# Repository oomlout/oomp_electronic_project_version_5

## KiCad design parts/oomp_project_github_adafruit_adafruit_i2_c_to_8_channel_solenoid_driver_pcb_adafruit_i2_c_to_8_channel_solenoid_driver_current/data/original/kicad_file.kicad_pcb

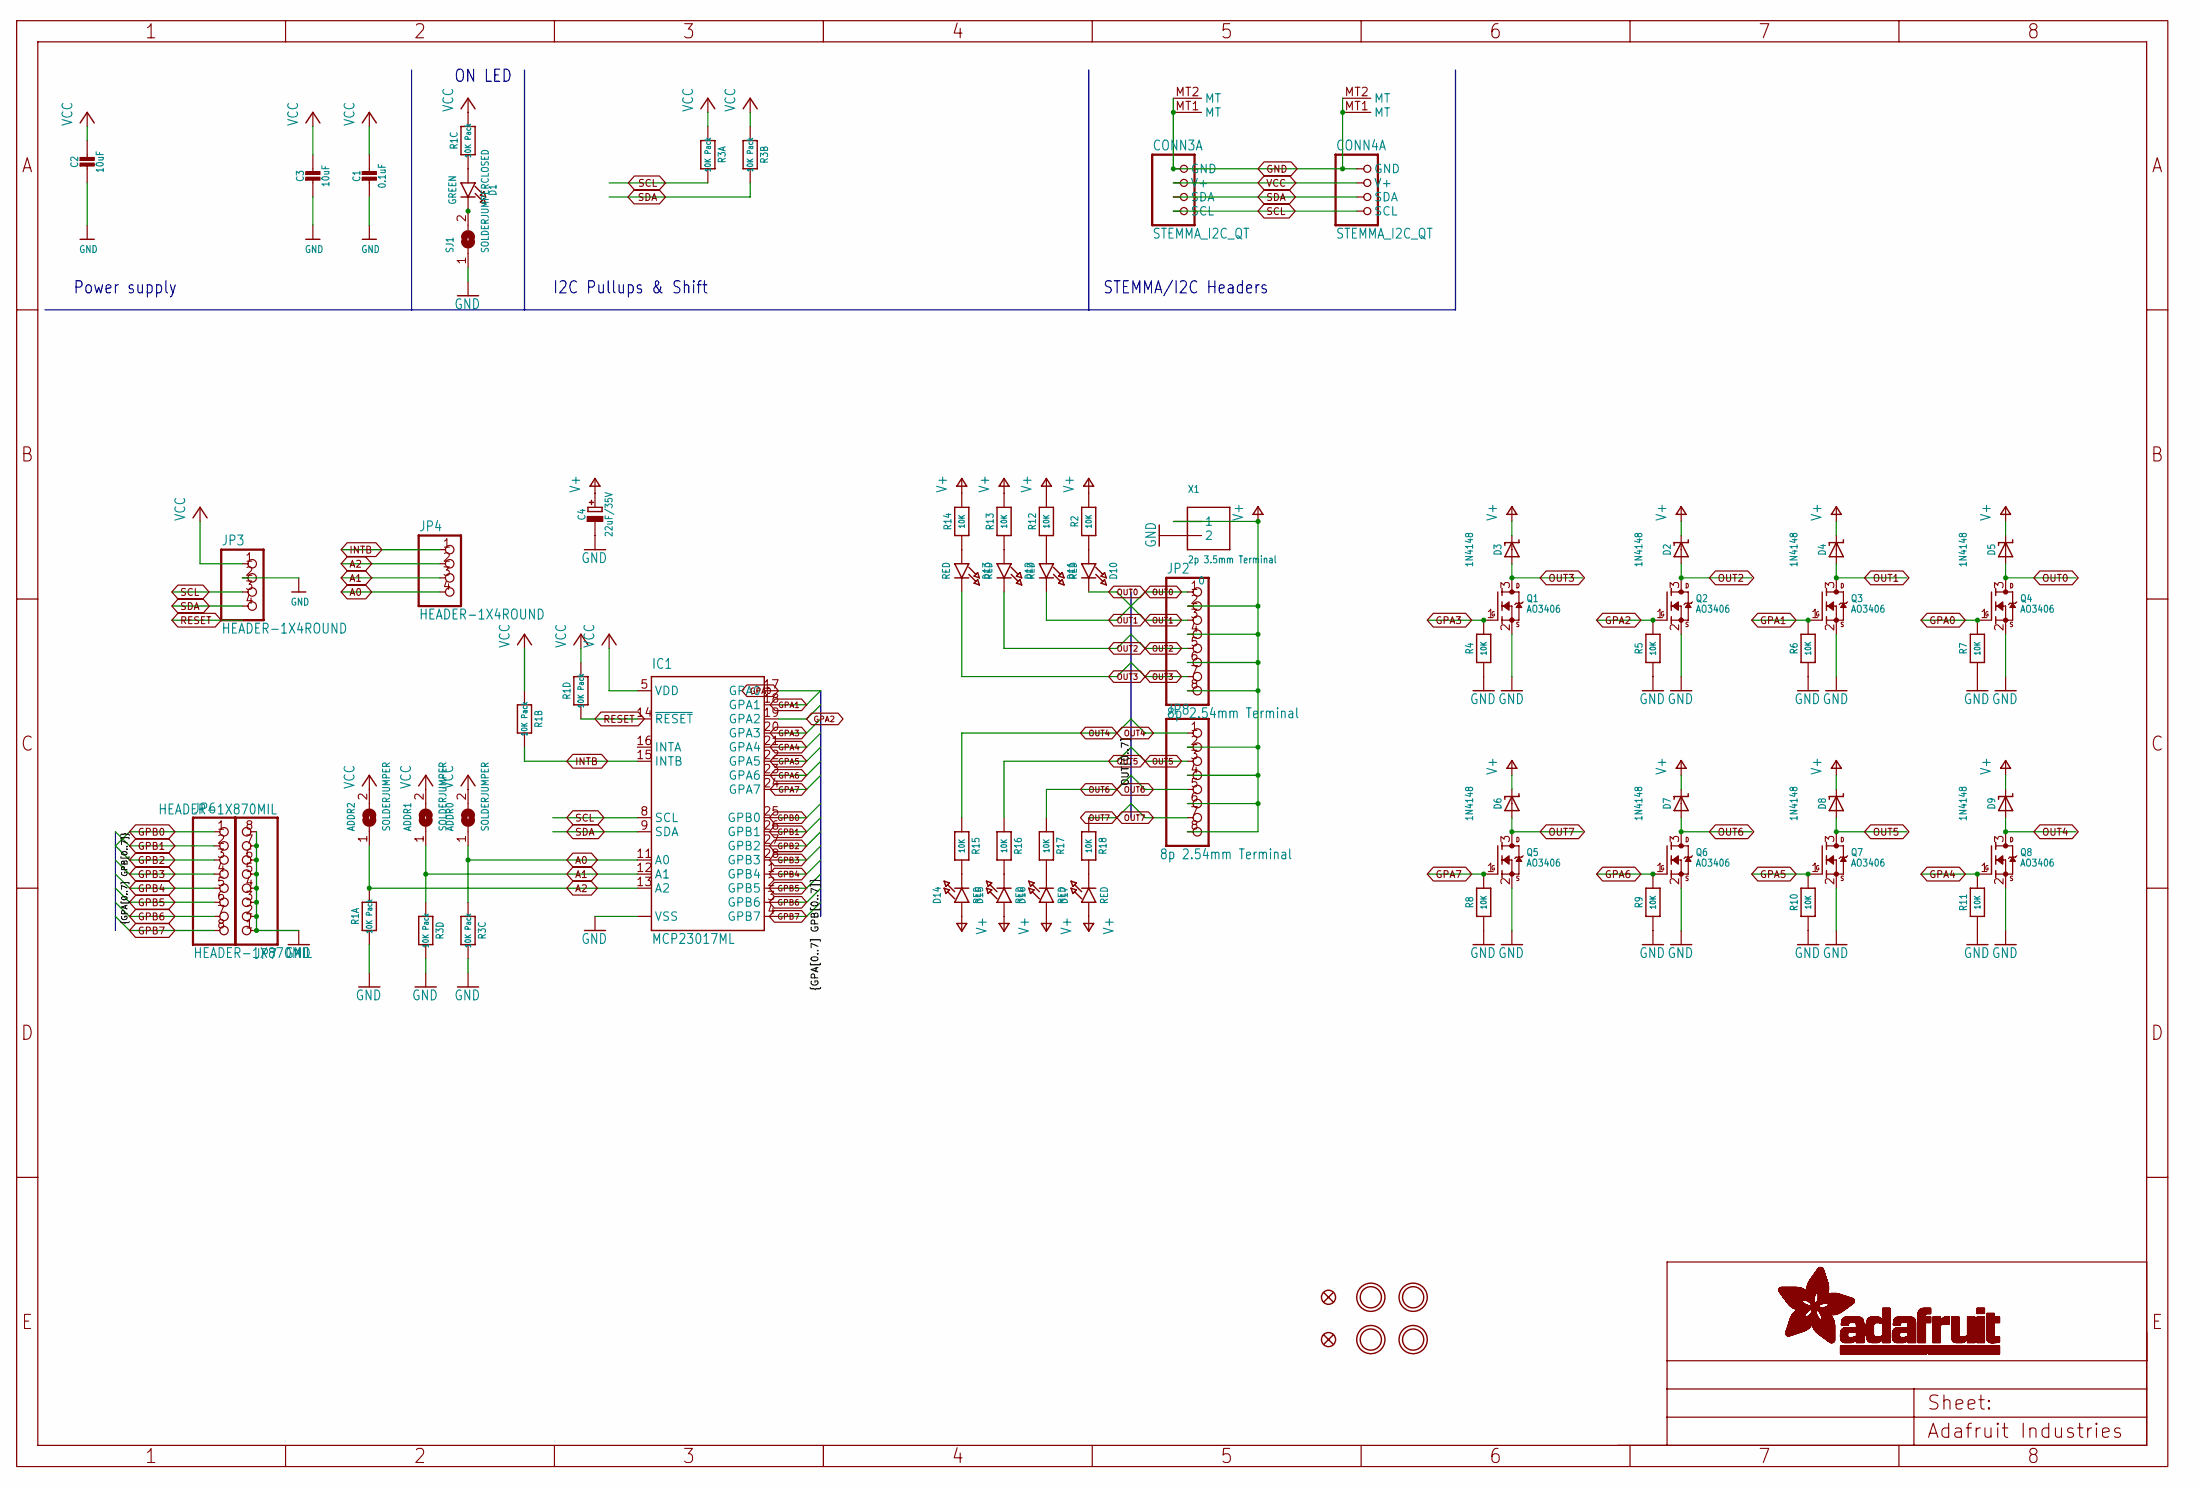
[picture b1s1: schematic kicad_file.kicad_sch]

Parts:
ADDR0, ADDR1, ADDR2: SOLDERJUMPER; SOLDERJUMPER_ARROW_NOPASTE
C1: 0.1uF; 0603-NO
C2, C3: 10uF; 0805-NO
C4: 22uF/35V; PANASONIC_C
CONN3, CONN4: STEMMA_I2C_QT; JST_SH4; LCSC C2845363
D1: GREEN; CHIPLED_0603_NOOUTLINE
D2, D3, D4, D5, D6, D7, D8, D9: 1N4148; SOD-323
D10, D11, D12, D13, D14, D15, D16, D17: RED; CHIPLED_0603_NOOUTLINE
FID3, FID4: FIDUCIAL_1MM
IC1: MCP23017ML; QFN28-ML_6X6MM; MPN MCP23017-E/ML
JP2, JP8: 8p 2.54mm Terminal; 1X08_2.54MMTERMINAL
JP3, JP4: HEADER-1X4ROUND; 1X04_ROUND
JP6, JP7: HEADER-1X870MIL; 1X08_ROUND_70
Q1, Q2, Q3, Q4, Q5, Q6, Q7, Q8: AO3406; SOT23-WIDE
R1, R3: 10K Pack; RESPACK_4X0603
R2, R4, R5, R6, R7, R8, R9, R10, R11, R12, R13, R14, R15, R16, R17, R18: 10K; 0603-NO
SJ1: SOLDERJUMPERCLOSED; SOLDERJUMPER_CLOSEDWIRE
U$1, U$17, U$19, U$21: MOUNTINGHOLE2.5; MOUNTINGHOLE_2.5_PLATED
X1: 2p 3.5mm Terminal; TERMBLOCK_1X2-3.5MM

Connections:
A0: ADDR0.1, IC1.11 (A0), JP4.4, R3.3 (1)
A1: ADDR1.1, IC1.12 (A1), JP4.3, R3.4 (1)
A2: ADDR2.1, IC1.13 (A2), JP4.2, R1.8 (2)
GND: C1.2, C2.2, C3.2, C4.-, CONN3.1 (GND), CONN3.MT1 (MT), CONN3.MT2 (MT), CONN4.1 (GND), CONN4.MT1 (MT), CONN4.MT2 (MT), IC1.6 (VSS), IC1.EXP (VSS), JP3.2, JP7.1, JP7.2, JP7.3, JP7.4, JP7.5, JP7.6, JP7.7, JP7.8, Q1.2 (S), Q2.2 (S), Q3.2 (S), Q4.2 (S), Q5.2 (S), Q6.2 (S), Q7.2 (S), Q8.2 (S), R1.1, R3.5 (2), R3.6 (2), R4.1, R5.1, R6.1, R7.1, R8.1, R9.1, R10.1, R11.1, SJ1.1, X1.2
GPA0: IC1.17 (GPA0), Q4.1 (G), R7.2
GPA1: IC1.18 (GPA1), Q3.1 (G), R6.2
GPA2: IC1.19 (GPA2), Q2.1 (G), R5.2
GPA3: IC1.20 (GPA3), Q1.1 (G), R4.2
GPA4: IC1.21 (GPA4), Q8.1 (G), R11.2
GPA5: IC1.22 (GPA5), Q7.1 (G), R10.2
GPA6: IC1.23 (GPA6), Q6.1 (G), R9.2
GPA7: IC1.24 (GPA7), Q5.1 (G), R8.2
GPB0: IC1.25 (GPB0), JP6.1
GPB1: IC1.26 (GPB1), JP6.2
GPB2: IC1.27 (GPB2), JP6.3
GPB3: IC1.28 (GPB3), JP6.4
GPB4: IC1.1 (GPB4), JP6.5
GPB5: IC1.2 (GPB5), JP6.6
GPB6: IC1.3 (GPB6), JP6.7
GPB7: IC1.4 (GPB7), JP6.8
INTB: IC1.15 (INTB), JP4.1, R1.7 (2)
unnamed: D1.A, R1.3 (1)
unnamed: D1.C, SJ1.2
unnamed: D10.A, R2.1
unnamed: D11.A, R12.1
unnamed: D12.A, R13.1
unnamed: D13.A, R14.1
unnamed: D14.C, R15.2
unnamed: D15.C, R16.2
unnamed: D16.C, R17.2
unnamed: D17.C, R18.2
OUT0: D5.A, D10.C, JP2.1, Q4.3 (D)
OUT1: D4.A, D11.C, JP2.3, Q3.3 (D)
OUT2: D2.A, D12.C, JP2.5, Q2.3 (D)
OUT3: D3.A, D13.C, JP2.7, Q1.3 (D)
OUT4: D9.A, JP8.1, Q8.3 (D), R15.1
OUT5: D8.A, JP8.3, Q7.3 (D), R16.1
OUT6: D7.A, JP8.5, Q6.3 (D), R17.1
OUT7: D6.A, JP8.7, Q5.3 (D), R18.1
RESET: IC1.14 (~RESET), R1.4 (1)
SCL: CONN3.4 (SCL), CONN4.4 (SCL), IC1.8 (SCL), JP3.3, R3.8 (2)
SDA: CONN3.3 (SDA), CONN4.3 (SDA), IC1.9 (SDA), JP3.4, R3.7 (2)
V+: C4.+, D2.C, D3.C, D4.C, D5.C, D6.C, D7.C, D8.C, D9.C, D14.A, D15.A, D16.A, D17.A, JP2.2, JP2.4, JP2.6, JP2.8, JP8.2, JP8.4, JP8.6, JP8.8, R2.2, R12.2, R13.2, R14.2, X1.1
VCC: ADDR0.2, ADDR1.2, ADDR2.2, C1.1, C2.1, C3.1, CONN3.2 (V+), CONN4.2 (V+), IC1.5 (VDD), JP3.1, R1.2 (1), R1.5 (2), R1.6 (2), R3.1, R3.2 (1)

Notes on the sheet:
STEMMA/I2C Headers
ON LED
I2C Pullups & Shift
Power supply

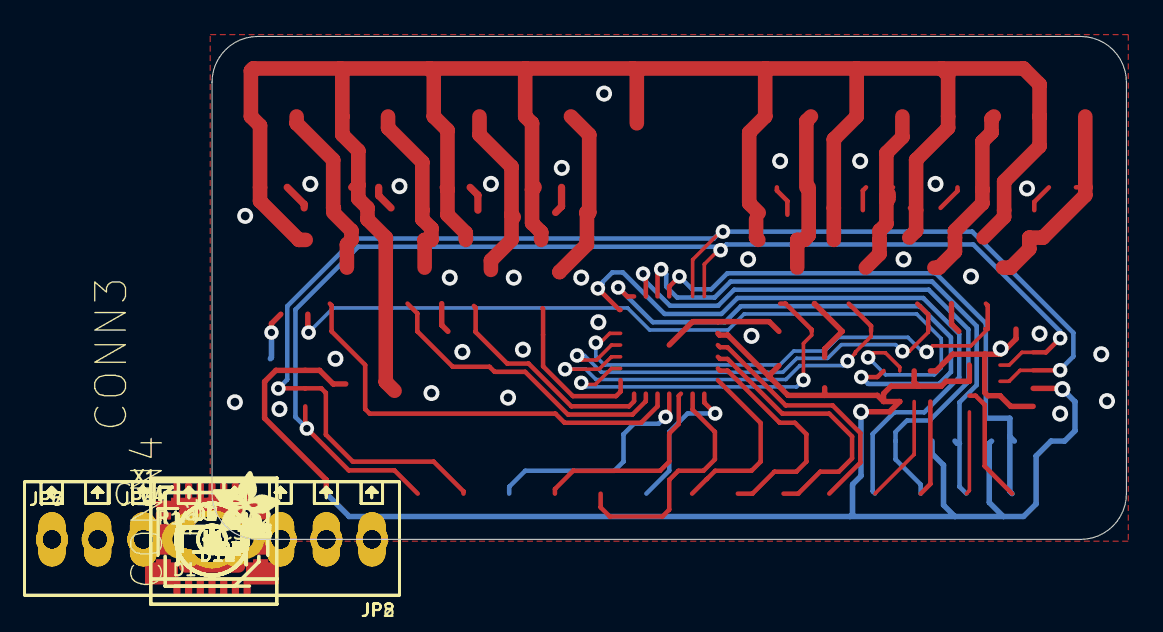
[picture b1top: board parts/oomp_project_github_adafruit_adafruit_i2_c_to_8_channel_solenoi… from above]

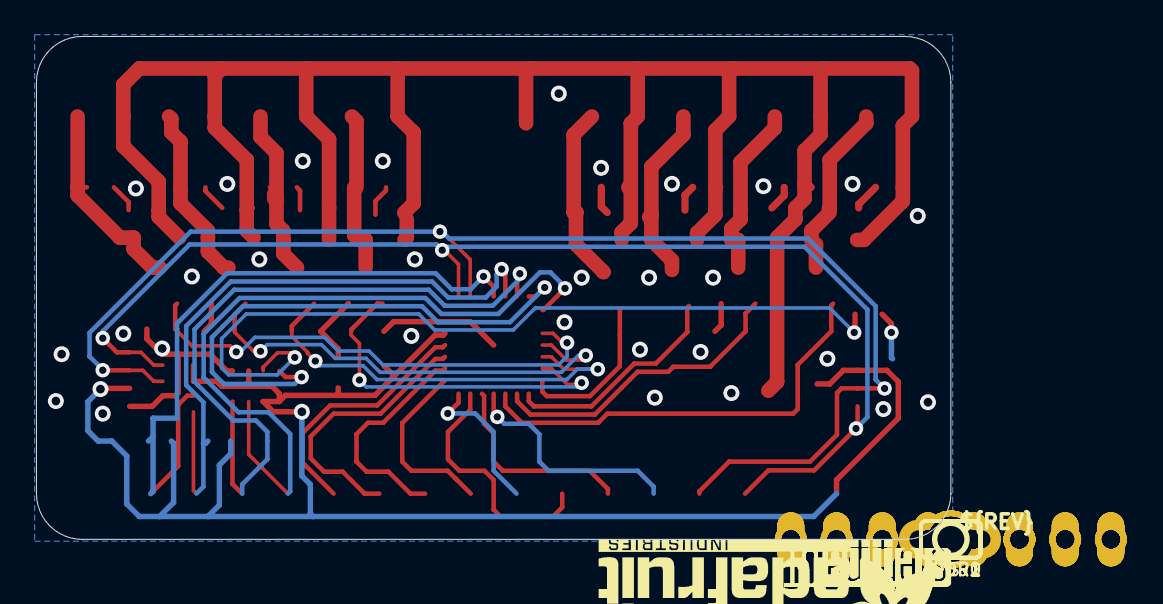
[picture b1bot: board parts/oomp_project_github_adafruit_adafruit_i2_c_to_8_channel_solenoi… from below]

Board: 2 copper layers, 50.8 x 27.9 mm, 135 parts (32 on the bottom side), 44 nets.

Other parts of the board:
PLABEL0: PLABEL0
PLABEL1: PLABEL1
PLABEL2: PLABEL2
PLABEL3: PLABEL3
PLABEL4: PLABEL4
PLABEL5: PLABEL5
PLABEL6: PLABEL6
PLABEL7: PLABEL7
PLABEL8: PLABEL8
PLABEL9: PLABEL9
PLABEL10: PLABEL10
PLABEL11: PLABEL11
PLABEL12: PLABEL12
PLABEL13: PLABEL13
PLABEL14: PLABEL14
PLABEL15: PLABEL15
PLABEL16: PLABEL16
PLABEL17: PLABEL17
PLABEL18: PLABEL18
PLABEL19: PLABEL19
PLABEL20: PLABEL20
PLABEL21: PLABEL21
PLABEL22: PLABEL22
PLABEL23: PLABEL23
PLABEL24: PLABEL24
PLABEL25: PLABEL25
PLABEL26: PLABEL26
PLABEL27: PLABEL27
PLABEL28: PLABEL28
PLABEL29: PLABEL29
PLABEL30: PLABEL30
PLABEL31: PLABEL31
PLABEL32: PLABEL32
PLABEL33: PLABEL33
PLABEL34: PLABEL34
PLABEL35: PLABEL35
PLABEL36: PLABEL36
PLABEL37: PLABEL37
PLABEL38: PLABEL38
PLABEL39: PLABEL39
PLABEL40: PLABEL40
PLABEL41: PLABEL41
PLABEL42: PLABEL42
PLABEL43: PLABEL43
PLABEL44: PLABEL44
PLABEL45: PLABEL45
PLABEL46: PLABEL46
PLABEL47: PLABEL47
PLABEL48: PLABEL48
PLABEL49: PLABEL49
PLABEL50: PLABEL50
PLABEL51: PLABEL51
PLABEL52: PLABEL52
PLABEL53: PLABEL53
PLABEL54: PLABEL54
PLABEL55: PLABEL55
PLABEL56: PLABEL56
PLABEL57: PLABEL57
PLABEL58: PLABEL58
PLABEL59: PLABEL59
PLABEL60: PLABEL60
U$2: PLUS; SYMBOL_PLUS
U$3: SYMBOL_MINUS
U$4: ADAFRUIT_3.5MM
U$7: ADAFRUIT_TEXT_20MM
U$25: PCBFEAT-REV-040
U$30, U$31: STEMMAQT

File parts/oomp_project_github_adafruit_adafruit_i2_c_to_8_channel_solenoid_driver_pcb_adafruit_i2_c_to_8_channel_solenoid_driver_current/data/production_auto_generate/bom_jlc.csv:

Comment,Designator,Footprint,LCSC Part #
,"JP3,JP4",Adafruit I2C to 8 Channel Solenoid Driver-import-fps:1X04_ROUND,C42431795
,"JP6,JP7",Adafruit I2C to 8 Channel Solenoid Driver-import-fps:1X08_ROUND_70,C492421
,U$4,Adafruit I2C to 8 Channel Solenoid Driver-import-fps:ADAFRUIT_3.5MM,
,U$7,Adafruit I2C to 8 Channel Solenoid Driver-import-fps:ADAFRUIT_TEXT_20MM,
,U$25,Adafruit I2C to 8 Channel Solenoid Driver-import-fps:PCBFEAT-REV-040,
,PLABEL0,Adafruit I2C to 8 Channel Solenoid Driver-import-fps:PLABEL0,
,PLABEL1,Adafruit I2C to 8 Channel Solenoid Driver-import-fps:PLABEL1,
,PLABEL10,Adafruit I2C to 8 Channel Solenoid Driver-import-fps:PLABEL10,
,PLABEL11,Adafruit I2C to 8 Channel Solenoid Driver-import-fps:PLABEL11,
,PLABEL12,Adafruit I2C to 8 Channel Solenoid Driver-import-fps:PLABEL12,
,PLABEL13,Adafruit I2C to 8 Channel Solenoid Driver-import-fps:PLABEL13,
,PLABEL14,Adafruit I2C to 8 Channel Solenoid Driver-import-fps:PLABEL14,
,PLABEL15,Adafruit I2C to 8 Channel Solenoid Driver-import-fps:PLABEL15,
,PLABEL16,Adafruit I2C to 8 Channel Solenoid Driver-import-fps:PLABEL16,
,PLABEL17,Adafruit I2C to 8 Channel Solenoid Driver-import-fps:PLABEL17,
,PLABEL18,Adafruit I2C to 8 Channel Solenoid Driver-import-fps:PLABEL18,
,PLABEL19,Adafruit I2C to 8 Channel Solenoid Driver-import-fps:PLABEL19,
,PLABEL2,Adafruit I2C to 8 Channel Solenoid Driver-import-fps:PLABEL2,
,PLABEL20,Adafruit I2C to 8 Channel Solenoid Driver-import-fps:PLABEL20,
,PLABEL21,Adafruit I2C to 8 Channel Solenoid Driver-import-fps:PLABEL21,
,PLABEL22,Adafruit I2C to 8 Channel Solenoid Driver-import-fps:PLABEL22,
,PLABEL23,Adafruit I2C to 8 Channel Solenoid Driver-import-fps:PLABEL23,
,PLABEL24,Adafruit I2C to 8 Channel Solenoid Driver-import-fps:PLABEL24,
,PLABEL25,Adafruit I2C to 8 Channel Solenoid Driver-import-fps:PLABEL25,
,PLABEL26,Adafruit I2C to 8 Channel Solenoid Driver-import-fps:PLABEL26,
,PLABEL27,Adafruit I2C to 8 Channel Solenoid Driver-import-fps:PLABEL27,
,PLABEL28,Adafruit I2C to 8 Channel Solenoid Driver-import-fps:PLABEL28,
,PLABEL29,Adafruit I2C to 8 Channel Solenoid Driver-import-fps:PLABEL29,
,PLABEL3,Adafruit I2C to 8 Channel Solenoid Driver-import-fps:PLABEL3,
,PLABEL30,Adafruit I2C to 8 Channel Solenoid Driver-import-fps:PLABEL30,
,PLABEL31,Adafruit I2C to 8 Channel Solenoid Driver-import-fps:PLABEL31,
,PLABEL32,Adafruit I2C to 8 Channel Solenoid Driver-import-fps:PLABEL32,
,PLABEL33,Adafruit I2C to 8 Channel Solenoid Driver-import-fps:PLABEL33,
,PLABEL34,Adafruit I2C to 8 Channel Solenoid Driver-import-fps:PLABEL34,
,PLABEL35,Adafruit I2C to 8 Channel Solenoid Driver-import-fps:PLABEL35,
,PLABEL36,Adafruit I2C to 8 Channel Solenoid Driver-import-fps:PLABEL36,
,PLABEL37,Adafruit I2C to 8 Channel Solenoid Driver-import-fps:PLABEL37,
,PLABEL38,Adafruit I2C to 8 Channel Solenoid Driver-import-fps:PLABEL38,
,PLABEL39,Adafruit I2C to 8 Channel Solenoid Driver-import-fps:PLABEL39,
,PLABEL4,Adafruit I2C to 8 Channel Solenoid Driver-import-fps:PLABEL4,
,PLABEL40,Adafruit I2C to 8 Channel Solenoid Driver-import-fps:PLABEL40,
,PLABEL41,Adafruit I2C to 8 Channel Solenoid Driver-import-fps:PLABEL41,
,PLABEL42,Adafruit I2C to 8 Channel Solenoid Driver-import-fps:PLABEL42,
,PLABEL43,Adafruit I2C to 8 Channel Solenoid Driver-import-fps:PLABEL43,
,PLABEL44,Adafruit I2C to 8 Channel Solenoid Driver-import-fps:PLABEL44,
,PLABEL45,Adafruit I2C to 8 Channel Solenoid Driver-import-fps:PLABEL45,
,PLABEL46,Adafruit I2C to 8 Channel Solenoid Driver-import-fps:PLABEL46,
,PLABEL47,Adafruit I2C to 8 Channel Solenoid Driver-import-fps:PLABEL47,
,PLABEL48,Adafruit I2C to 8 Channel Solenoid Driver-import-fps:PLABEL48,
,PLABEL49,Adafruit I2C to 8 Channel Solenoid Driver-import-fps:PLABEL49,
,PLABEL5,Adafruit I2C to 8 Channel Solenoid Driver-import-fps:PLABEL5,
,PLABEL50,Adafruit I2C to 8 Channel Solenoid Driver-import-fps:PLABEL50,
,PLABEL51,Adafruit I2C to 8 Channel Solenoid Driver-import-fps:PLABEL51,
,PLABEL52,Adafruit I2C to 8 Channel Solenoid Driver-import-fps:PLABEL52,
,PLABEL53,Adafruit I2C to 8 Channel Solenoid Driver-import-fps:PLABEL53,
,PLABEL54,Adafruit I2C to 8 Channel Solenoid Driver-import-fps:PLABEL54,
,PLABEL55,Adafruit I2C to 8 Channel Solenoid Driver-import-fps:PLABEL55,
,PLABEL56,Adafruit I2C to 8 Channel Solenoid Driver-import-fps:PLABEL56,
,PLABEL57,Adafruit I2C to 8 Channel Solenoid Driver-import-fps:PLABEL57,
,PLABEL58,Adafruit I2C to 8 Channel Solenoid Driver-import-fps:PLABEL58,
,PLABEL59,Adafruit I2C to 8 Channel Solenoid Driver-import-fps:PLABEL59,
,PLABEL6,Adafruit I2C to 8 Channel Solenoid Driver-import-fps:PLABEL6,
,PLABEL60,Adafruit I2C to 8 Channel Solenoid Driver-import-fps:PLABEL60,
,PLABEL7,Adafruit I2C to 8 Channel Solenoid Driver-import-fps:PLABEL7,
,PLABEL8,Adafruit I2C to 8 Channel Solenoid Driver-import-fps:PLABEL8,
,PLABEL9,Adafruit I2C to 8 Channel Solenoid Driver-import-fps:PLABEL9,
,"ADDR0,ADDR1,ADDR2",Adafruit I2C to 8 Channel Solenoid Driver-import-fps:SOLDERJUMPER_ARROW_NOPASTE,
,"U$30,U$31",Adafruit I2C to 8 Channel Solenoid Driver-import-fps:STEMMAQT,
,U$3,Adafruit I2C to 8 Channel Solenoid Driver-import-fps:SYMBOL_MINUS,
0.1uF,C1,Adafruit I2C to 8 Channel Solenoid Driver-import-fps:0603-NO,C14663
10K,"R2,R4,R5,R6,R7,R8,R9,R10,R11,R12,R13,R14,R15,R16,R17,R18",Adafruit I2C to 8 Channel Solenoid Driver-import-fps:0603-NO,C98220
10K Pack,"R1,R3",Adafruit I2C to 8 Channel Solenoid Driver-import-fps:RESPACK_4X0603,C98220
10uF,"C2,C3",Adafruit I2C to 8 Channel Solenoid Driver-import-fps:0805-NO,
1N4148,"D2,D3,D4,D5,D6,D7,D8,D9",Adafruit I2C to 8 Channel Solenoid Driver-import-fps:SOD-323,
22uF/35V,C4,Adafruit I2C to 8 Channel Solenoid Driver-import-fps:PANASONIC_C,
2p 3.5mm Terminal,X1,Adafruit I2C to 8 Channel Solenoid Driver-import-fps:TERMBLOCK_1X2-3.5MM,
8p 2.54mm Terminal,"JP2,JP8",Adafruit I2C to 8 Channel Solenoid Driver-import-fps:1X08_2.54MMTERMINAL,C492421
AO3406,"Q1,Q2,Q3,Q4,Q5,Q6,Q7,Q8",Adafruit I2C to 8 Channel Solenoid Driver-import-fps:SOT23-WIDE,
GREEN,D1,Adafruit I2C to 8 Channel Solenoid Driver-import-fps:CHIPLED_0603_NOOUTLINE,
MCP23017ML,IC1,Adafruit I2C to 8 Channel Solenoid Driver-import-fps:QFN28-ML_6X6MM,
PLUS,U$2,Adafruit I2C to 8 Channel Solenoid Driver-import-fps:SYMBOL_PLUS,
RED,"D10,D11,D12,D13,D14,D15,D16,D17",Adafruit I2C to 8 Channel Solenoid Driver-import-fps:CHIPLED_0603_NOOUTLINE,
STEMMA_I2C_QT,"CONN3,CONN4",Adafruit I2C to 8 Channel Solenoid Driver-import-fps:JST_SH4,C160404

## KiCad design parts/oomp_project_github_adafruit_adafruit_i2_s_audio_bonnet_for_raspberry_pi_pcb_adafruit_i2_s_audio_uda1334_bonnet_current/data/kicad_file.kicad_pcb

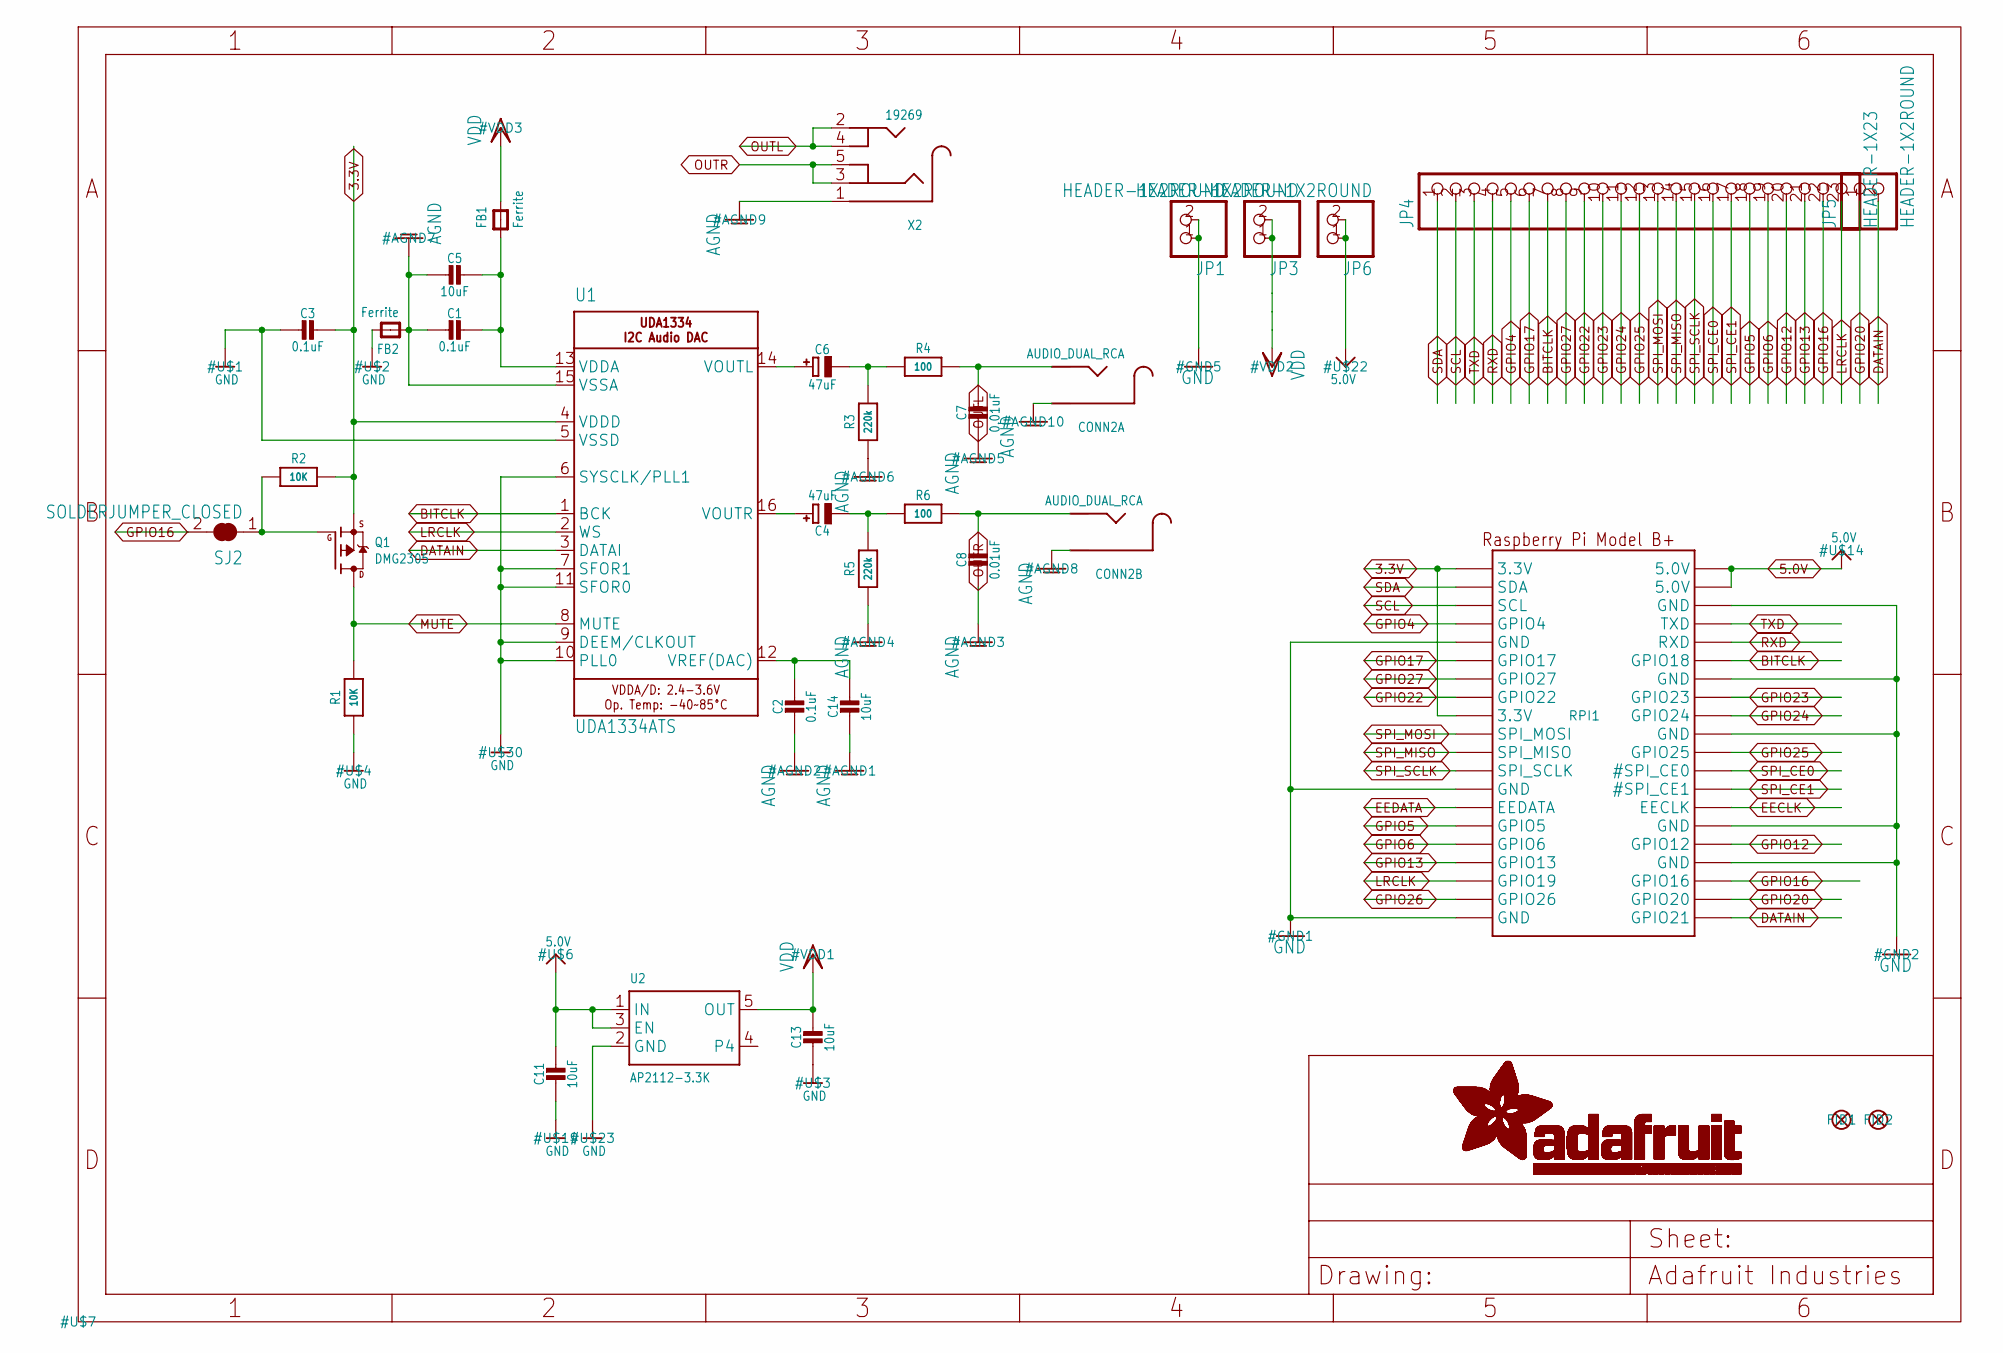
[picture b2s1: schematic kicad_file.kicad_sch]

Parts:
C1, C2, C3: 0.1uF; 0603-NO
C4, C6: 47uF; PANASONIC_C
C5, C11, C13, C14: 10uF; 0805-NO
C7, C8: 0.01uF; 0603-NO
CONN2: AUDIO_DUAL_RCA; RCA_DUAL_JACK
FB1, FB2: Ferrite; 0805
FID1, FID2: FIDUCIAL_1MM
JP1, JP3, JP5, JP6: HEADER-1X2ROUND; 1X02_ROUND
JP4: HEADER-1X23; 1X23_ROUND_70MIL
Q1: DMG2305; SOT23-WIDE
R1, R2: 10K; 0603-NO
R3, R5: 220k; 0603-NO
R4, R6: 100; 0603-NO
RPI1: RASPBERRYPI_BPLUS_BONNET_THMSMT; PI_BONNET_THMSMT
SJ2: SOLDERJUMPER_CLOSED; SOLDERJUMPER_CLOSEDWIRE
U1: UDA1334ATS; SSOP16_4.4MM
U2: AP2112-3.3K; SOT23-5
X2: 19269; 4UCONN_19269

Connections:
3.3V: C3.1, Q1.2 (S), R2.2, RPI1.1 (3.3V), RPI1.17 (3.3V), RPI1.S1 (3.3V), RPI1.S17 (3.3V), U1.4 (VDDD)
5.0V: C11.1, JP6.1, JP6.2, RPI1.2 (5.0V), RPI1.4 (5.0V), RPI1.S2 (5.0V), RPI1.S4 (5.0V), U2.1 (IN), U2.3 (EN)
AGND: C1.2, C2.2, C5.2, C7.2, C8.2, C14.2, CONN2.L_G (SLEEVE), CONN2.L_G' (SLEEVE), CONN2.R_G (SLEEVE), CONN2.R_G' (SLEEVE), FB2.1, R3.1, R5.1, U1.15 (VSSA), X2.1
BITCLK: JP4.7, RPI1.12 (GPIO18), RPI1.S12 (GPIO18), U1.1 (BCK)
DATAIN: JP5.2, RPI1.40 (GPIO21), RPI1.S40 (GPIO21), U1.3 (DATAI)
EECLK: RPI1.28 (EECLK), RPI1.S28 (EECLK)
EEDATA: RPI1.27 (EEDATA), RPI1.S27 (EEDATA)
GND: C3.2, C11.2, C13.2, FB2.2, JP1.1, JP1.2, R1.1, RPI1.6 (GND), RPI1.9 (GND), RPI1.14 (GND), RPI1.20 (GND), RPI1.25 (GND), RPI1.30 (GND), RPI1.34 (GND), RPI1.39 (GND), RPI1.S6 (GND), RPI1.S9 (GND), RPI1.S14 (GND), RPI1.S20 (GND), RPI1.S25 (GND), RPI1.S30 (GND), RPI1.S34 (GND), RPI1.S39 (GND), U1.5 (VSSD), U1.6 (SYSCLK/PLL1), U1.7 (SFOR1), U1.9 (DEEM/CLKOUT), U1.10 (PLL0), U1.11 (SFOR0), U2.2 (GND)
GPIO4: JP4.5, RPI1.7 (GPIO4), RPI1.S7 (GPIO4)
GPIO5: JP4.18, RPI1.29 (GPIO5), RPI1.S29 (GPIO5)
GPIO6: JP4.19, RPI1.31 (GPIO6), RPI1.S31 (GPIO6)
GPIO12: JP4.20, RPI1.32 (GPIO12), RPI1.S32 (GPIO12)
GPIO13: JP4.21, RPI1.33 (GPIO13), RPI1.S33 (GPIO13)
GPIO16: JP4.22, RPI1.36 (GPIO16), RPI1.S36 (GPIO16), SJ2.2
GPIO17: JP4.6, RPI1.11 (GPIO17), RPI1.S11 (GPIO17)
GPIO20: JP5.1, RPI1.38 (GPIO20), RPI1.S38 (GPIO20)
GPIO22: JP4.9, RPI1.15 (GPIO22), RPI1.S15 (GPIO22)
GPIO23: JP4.10, RPI1.16 (GPIO23), RPI1.S16 (GPIO23)
GPIO24: JP4.11, RPI1.18 (GPIO24), RPI1.S18 (GPIO24)
GPIO25: JP4.12, RPI1.22 (GPIO25), RPI1.S22 (GPIO25)
GPIO26: RPI1.37 (GPIO26), RPI1.S37 (GPIO26)
GPIO27: JP4.8, RPI1.13 (GPIO27), RPI1.S13 (GPIO27)
LRCLK: JP4.23, RPI1.35 (GPIO19), RPI1.S35 (GPIO19), U1.2 (WS)
MUTE: Q1.3 (D), R1.2, U1.8 (MUTE)
unnamed: C2.1, C14.1, U1.12 (VREF(DAC))
unnamed: C1.1, C5.1, FB1.1, U1.13 (VDDA)
unnamed: C4.+, U1.16 (VOUTR)
unnamed: Q1.1 (G), R2.1, SJ2.1
unnamed: C6.+, U1.14 (VOUTL)
unnamed: C6.-, R3.2, R4.1
unnamed: C4.-, R5.2, R6.1
OUTL: C7.1, CONN2.L_SIG (TIP), CONN2.L_SIG' (TIP), R4.2, X2.2, X2.4
OUTR: C8.1, CONN2.R_SIG (TIP), CONN2.R_SIG' (TIP), R6.2, X2.3, X2.5
RXD: JP4.4, RPI1.10 (RXD), RPI1.S10 (RXD)
SCL: JP4.2, RPI1.5 (SCL), RPI1.S5 (SCL)
SDA: JP4.1, RPI1.3 (SDA), RPI1.S3 (SDA)
SPI_CE0: JP4.16, RPI1.24 (#SPI_CE0), RPI1.S24 (#SPI_CE0)
SPI_CE1: JP4.17, RPI1.26 (#SPI_CE1), RPI1.S26 (#SPI_CE1)
SPI_MISO: JP4.14, RPI1.21 (SPI_MISO), RPI1.S21 (SPI_MISO)
SPI_MOSI: JP4.13, RPI1.19 (SPI_MOSI), RPI1.S19 (SPI_MOSI)
SPI_SCLK: JP4.15, RPI1.23 (SPI_SCLK), RPI1.S23 (SPI_SCLK)
TXD: JP4.3, RPI1.8 (TXD), RPI1.S8 (TXD)
VDD: C13.1, FB1.2, JP3.1, JP3.2, U2.5 (OUT)

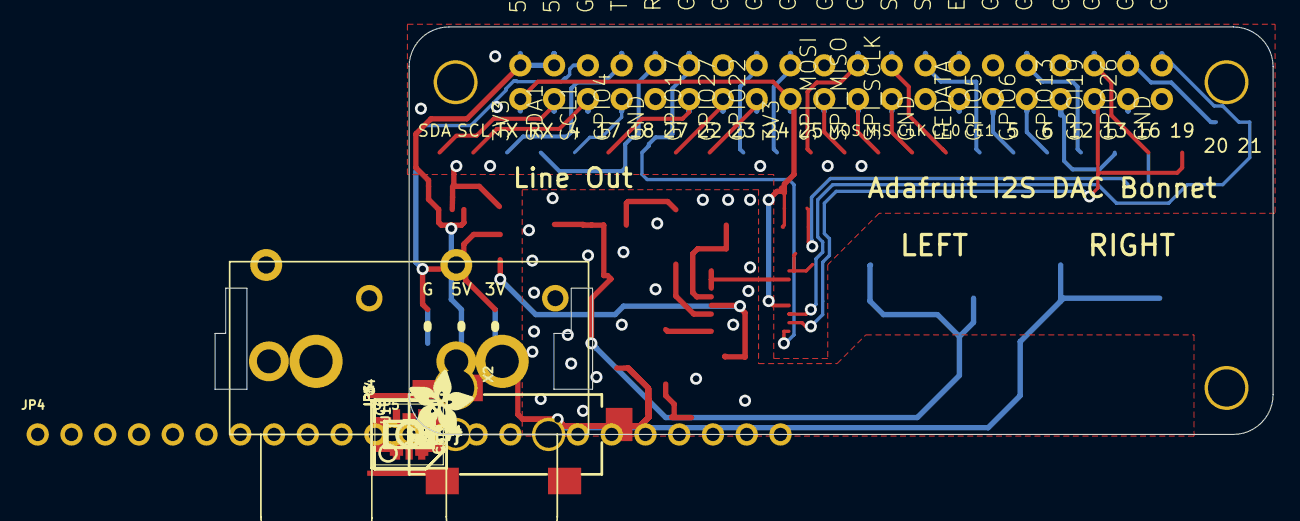
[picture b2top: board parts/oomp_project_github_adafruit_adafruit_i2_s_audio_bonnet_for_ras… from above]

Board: 2 copper layers, 65.0 x 30.7 mm, 35 parts (1 on the bottom side), 43 nets.

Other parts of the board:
U$5: ADAFRUIT_5MM
U$11: PCBFEAT-REV-040

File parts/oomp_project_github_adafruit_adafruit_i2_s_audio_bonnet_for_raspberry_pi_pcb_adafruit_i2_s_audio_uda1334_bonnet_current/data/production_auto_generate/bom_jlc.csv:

Comment,Designator,Footprint,LCSC Part #
,"JP1,JP3,JP5,JP6",Adafruit I2S Audio UDA1334 Bonnet-import-fps:1X02_ROUND,C492401
,JP4,Adafruit I2S Audio UDA1334 Bonnet-import-fps:1X23_ROUND_70MIL,C725915
,U$5,Adafruit I2S Audio UDA1334 Bonnet-import-fps:ADAFRUIT_5MM,
,U$11,Adafruit I2S Audio UDA1334 Bonnet-import-fps:PCBFEAT-REV-040,
 DMG2305,Q1,Adafruit I2S Audio UDA1334 Bonnet-import-fps:SOT23-WIDE,
0.01uF,"C7,C8",Adafruit I2S Audio UDA1334 Bonnet-import-fps:0603-NO,C5137477
0.1uF,"C1,C2,C3",Adafruit I2S Audio UDA1334 Bonnet-import-fps:0603-NO,C14663
100,"R4,R6",Adafruit I2S Audio UDA1334 Bonnet-import-fps:0603-NO,C22775
10K,"R1,R2",Adafruit I2S Audio UDA1334 Bonnet-import-fps:0603-NO,C98220
10uF,"C5,C11,C13,C14",Adafruit I2S Audio UDA1334 Bonnet-import-fps:0805-NO,
19269,X2,Adafruit I2S Audio UDA1334 Bonnet-import-fps:4UCONN_19269,
220k,"R3,R5",Adafruit I2S Audio UDA1334 Bonnet-import-fps:0603-NO,C2907013
47uF,"C4,C6",Adafruit I2S Audio UDA1334 Bonnet-import-fps:PANASONIC_C,
AP2112-3.3K,U2,Adafruit I2S Audio UDA1334 Bonnet-import-fps:SOT23-5,
AUDIO_DUAL_RCA,CONN2,Adafruit I2S Audio UDA1334 Bonnet-import-fps:RCA_DUAL_JACK,
Ferrite,"FB1,FB2",Adafruit I2S Audio UDA1334 Bonnet-import-fps:0805,
RASPBERRYPI_BPLUS_BONNET_THMSMT,RPI1,Adafruit I2S Audio UDA1334 Bonnet-import-fps:PI_BONNET_THMSMT,
UDA1334ATS,U1,Adafruit I2S Audio UDA1334 Bonnet-import-fps:SSOP16_4.4MM,

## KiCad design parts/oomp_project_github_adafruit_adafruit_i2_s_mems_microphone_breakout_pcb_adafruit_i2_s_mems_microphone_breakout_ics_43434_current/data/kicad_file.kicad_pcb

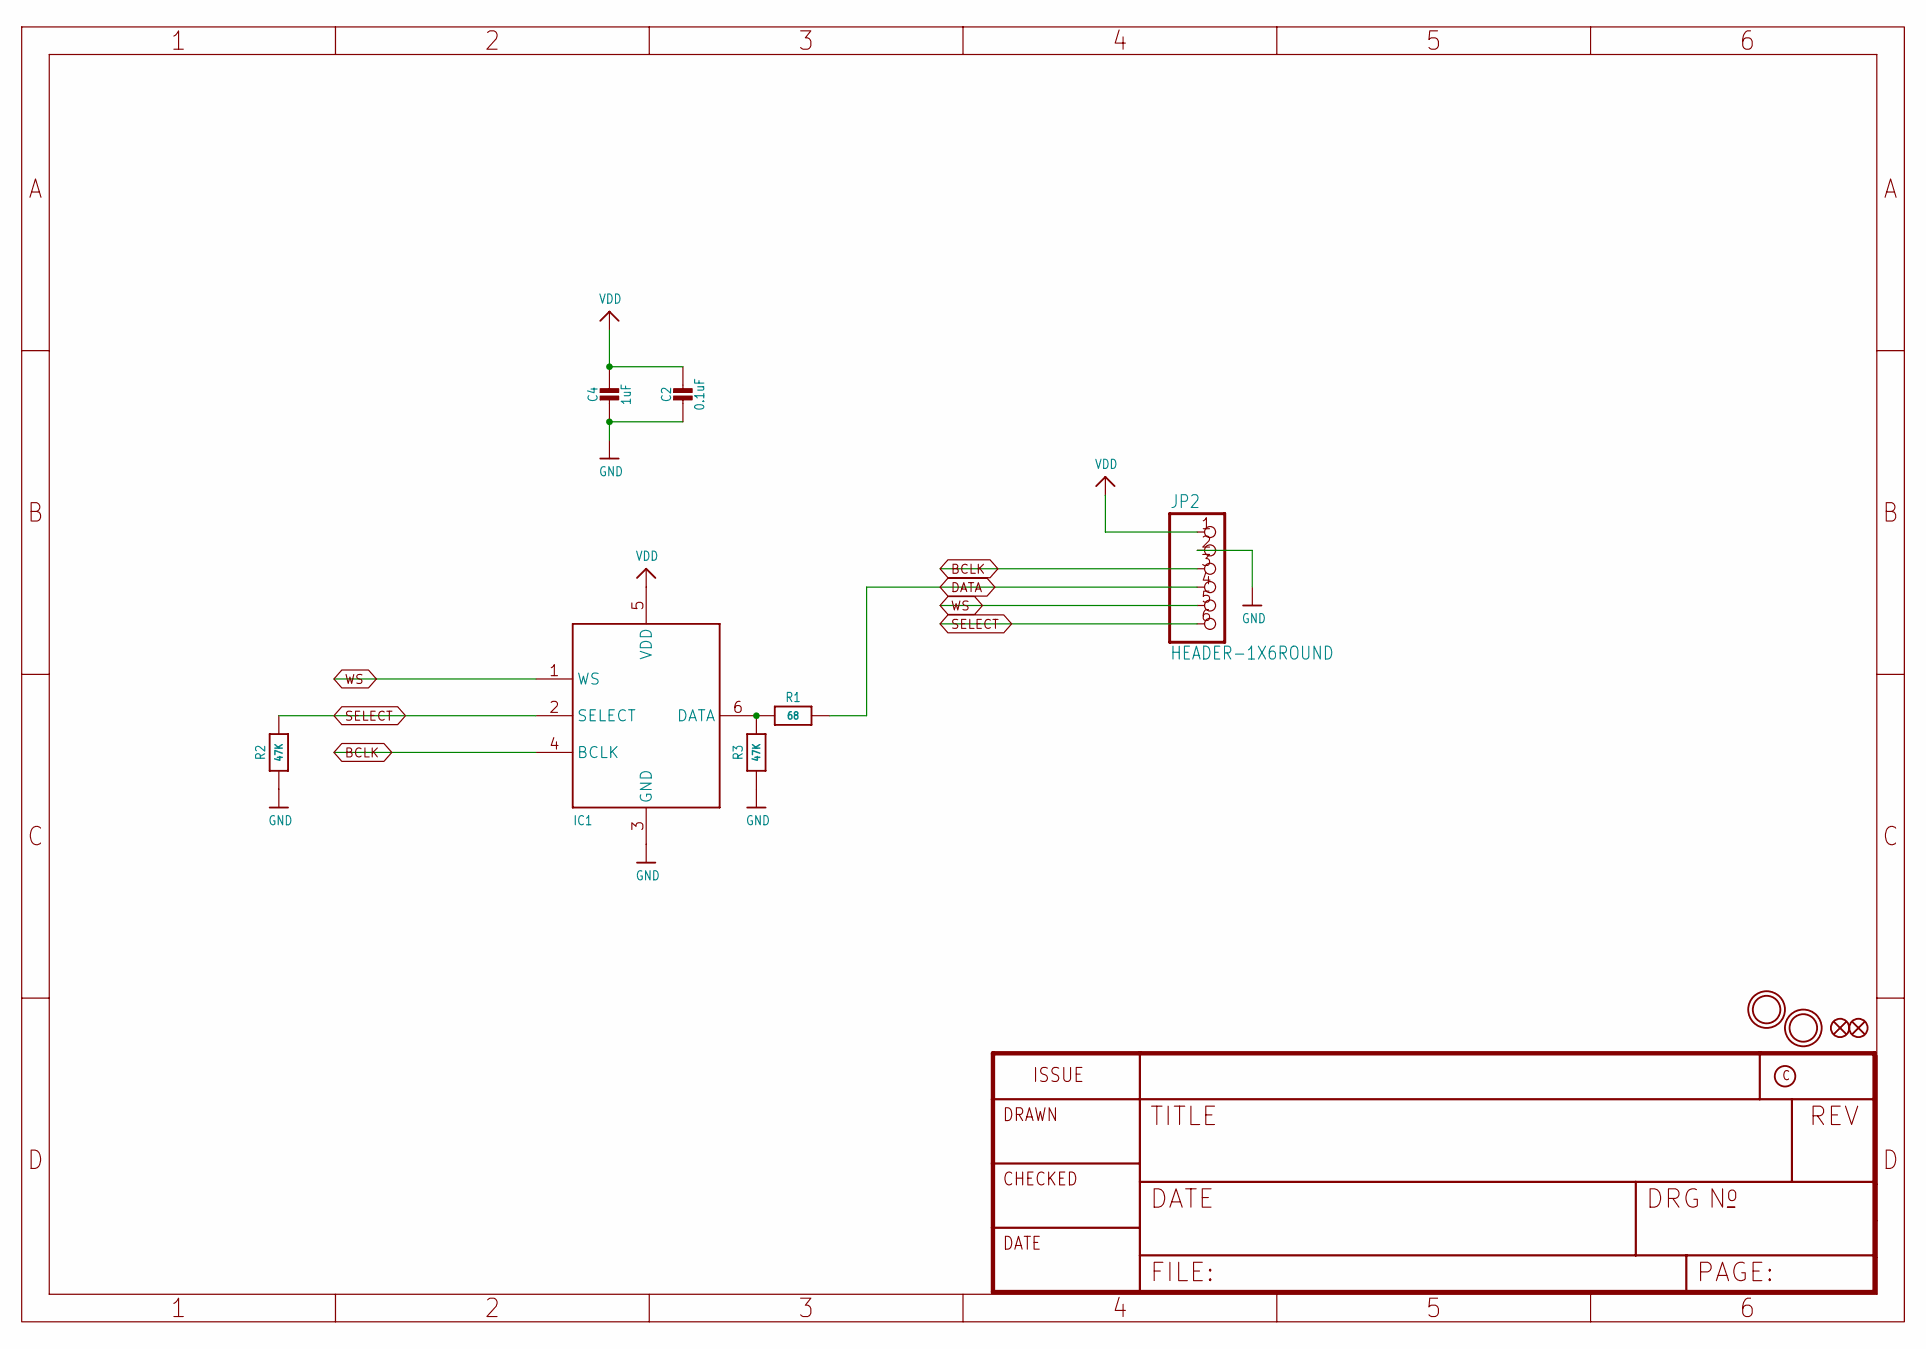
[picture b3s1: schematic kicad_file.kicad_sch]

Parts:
C2: 0.1uF; 0603-NO
C4: 1uF; 0603-NO
FID1, FID2: FIDUCIAL_0.5MM
IC1: ICS-43434; SPH0645LM4H
JP2: HEADER-1X6ROUND; 1X06_ROUND
R1: 68; 0603-NO
R2, R3: 47K; 0603-NO
U$6, U$12: MOUNTINGHOLE2.5; MOUNTINGHOLE_2.5_PLATED

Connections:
BCLK: IC1.4 (BCLK), JP2.3
DATA: JP2.4, R1.2
GND: C2.2, C4.2, IC1.3 (GND), JP2.2, R2.1, R3.1
unnamed: IC1.6 (DATA), R1.1, R3.2
SELECT: IC1.2 (SELECT), JP2.6, R2.2
VDD: C2.1, C4.1, IC1.5 (VDD), JP2.1
WS: IC1.1 (WS), JP2.5

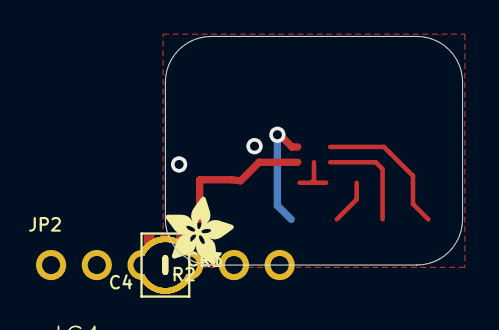
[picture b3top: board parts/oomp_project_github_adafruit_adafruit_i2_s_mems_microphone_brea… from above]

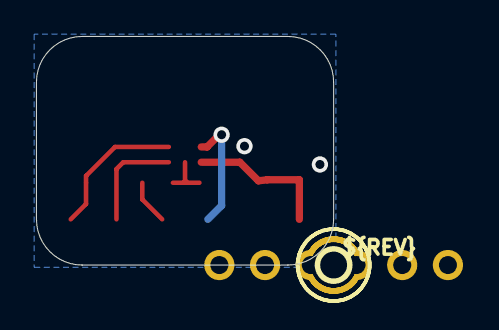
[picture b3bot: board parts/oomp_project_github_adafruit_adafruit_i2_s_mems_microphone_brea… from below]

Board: 2 copper layers, 16.5 x 12.7 mm, 23 parts (11 on the bottom side), 7 nets.

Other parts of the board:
PLABEL0: PLABEL0
PLABEL1: PLABEL1
PLABEL2: PLABEL2
PLABEL3: PLABEL3
PLABEL4: PLABEL4
PLABEL5: PLABEL5
PLABEL7: PLABEL7
PLABEL8: PLABEL8
PLABEL9: PLABEL9
PLABEL10: PLABEL10
U$5: ADAFRUIT_3.5MM
U$13: PCBFEAT-REV-040

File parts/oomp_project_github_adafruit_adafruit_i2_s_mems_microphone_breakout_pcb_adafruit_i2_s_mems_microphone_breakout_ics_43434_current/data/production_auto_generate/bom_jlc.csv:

Comment,Designator,Footprint,LCSC Part #
,JP2,Adafruit I2S MEMS Microphone Breakout - ICS-43434-import-fps:1X06_ROUND,C37208
,U$5,Adafruit I2S MEMS Microphone Breakout - ICS-43434-import-fps:ADAFRUIT_3.5MM,
,U$13,Adafruit I2S MEMS Microphone Breakout - ICS-43434-import-fps:PCBFEAT-REV-040,
,PLABEL0,Adafruit I2S MEMS Microphone Breakout - ICS-43434-import-fps:PLABEL0,
,PLABEL1,Adafruit I2S MEMS Microphone Breakout - ICS-43434-import-fps:PLABEL1,
,PLABEL10,Adafruit I2S MEMS Microphone Breakout - ICS-43434-import-fps:PLABEL10,
,PLABEL2,Adafruit I2S MEMS Microphone Breakout - ICS-43434-import-fps:PLABEL2,
,PLABEL3,Adafruit I2S MEMS Microphone Breakout - ICS-43434-import-fps:PLABEL3,
,PLABEL4,Adafruit I2S MEMS Microphone Breakout - ICS-43434-import-fps:PLABEL4,
,PLABEL5,Adafruit I2S MEMS Microphone Breakout - ICS-43434-import-fps:PLABEL5,
,PLABEL7,Adafruit I2S MEMS Microphone Breakout - ICS-43434-import-fps:PLABEL7,
,PLABEL8,Adafruit I2S MEMS Microphone Breakout - ICS-43434-import-fps:PLABEL8,
,PLABEL9,Adafruit I2S MEMS Microphone Breakout - ICS-43434-import-fps:PLABEL9,
0.1uF,C2,Adafruit I2S MEMS Microphone Breakout - ICS-43434-import-fps:0603-NO,C14663
1uF,C4,Adafruit I2S MEMS Microphone Breakout - ICS-43434-import-fps:0603-NO,C5673
47K,"R2,R3",Adafruit I2S MEMS Microphone Breakout - ICS-43434-import-fps:0603-NO,C2907042
68,R1,Adafruit I2S MEMS Microphone Breakout - ICS-43434-import-fps:0603-NO,C27592
ICS-43434,IC1,Adafruit I2S MEMS Microphone Breakout - ICS-43434-import-fps:SPH0645LM4H,

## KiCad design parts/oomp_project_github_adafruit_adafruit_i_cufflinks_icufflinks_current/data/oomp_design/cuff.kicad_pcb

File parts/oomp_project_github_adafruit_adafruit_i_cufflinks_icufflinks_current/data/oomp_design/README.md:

# OOMP KiCad design copy

Open `cuff.kicad_pro` (or the `.kicad_pcb` / `.kicad_sch`) in KiCad. Local OOMP libraries are under `libraries/`. Original inputs are preserved in [../original/](../original/).

Only verified unchanged installed KiCad defaults were renamed. Modified, custom, unmatched and unavailable items remain unchanged. Soldering variants are never swapped during conversion. Existing pad coordinates, nets and UUIDs are preserved.

See [conversion_report.yaml](conversion_report.yaml) for every conversion and skip. Copy this directory before editing; regeneration refuses to overwrite edited design files.

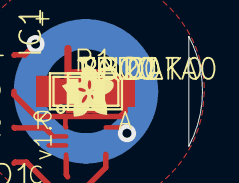
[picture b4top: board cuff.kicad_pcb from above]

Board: 2 copper layers, 12 parts (0 on the bottom side), 7 nets.

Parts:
GND0: TPTP10R; TP10R
IC1: ATTINY10-MAHR; UDFN-8
LED1: SMLK34
PB2: TPTP10R; TP10R
R1: R0805
RST0: TPTP10R; TP10R
TPICLK0: TPTP10R; TP10R
TPIDATA0: TPTP10R; TP10R
U$1: ADAFRUIT200MIL
U$2, U$3: FIDUCIAL; TP_SIGNAL_NAME!
VCC0: TPTP10R; TP10R

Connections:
B0: IC1.5, LED1.K, TPIDATA0.TP
B1: IC1.1, TPICLK0.TP
B2: IC1.8, PB2.TP
GND: GND0.TP, IC1.4
unnamed: LED1.A, R1.1
RST: IC1.6, RST0.TP
VCC: IC1.7, R1.2, VCC0.TP

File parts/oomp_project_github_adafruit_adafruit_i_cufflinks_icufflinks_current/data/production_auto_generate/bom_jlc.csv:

Comment,Designator,Footprint,LCSC Part #
,U$1,cuff-import-fps:ADAFRUIT200MIL,
,R1,cuff-import-fps:R0805,
,LED1,cuff-import-fps:SMLK34,
ATTINY10-MAHR,IC1,cuff-import-fps:UDFN-8,
FIDUCIAL,"U$2,U$3",cuff-import-fps:TP_SIGNAL_NAME!,
TPTP10R,"GND0,PB2,RST0,TPICLK0,TPIDATA0,VCC0",cuff-import-fps:TP10R,
